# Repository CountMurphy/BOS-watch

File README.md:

Brotherhood of Steel Watch
========================

Ad Victoriam brother!

The BOS watch is the second version of my GPS enabled wristwatches. Stripped of the non used features and annoyances of the [Pipman](https://random-hackery.net/post/pipman-gps-watch/) , the BOS watch contains all things a man traveling the wastes could want

[Official Page](https://random-hackery.net/post/bos-watch/)

Features
---------------
- GPS time syncing - get local time anywhere on earth at power up

- Tilt compensated compass (with LED directional indicators and exact heading information)

- Stop watch / countdown timer

- Speaker (Plays the fallout theme!)

- TV B-gone

- A Frickn' Laser!&trade;

- Low power usage

- USB charging

-  Gieger Counter sound emulator (planned at least)

- Retro look and feel using custom DIP switches (with 7 operating modes) and 1970's era calculator display bubble LEDs

Tech
---------
The BOS watch uses an arm processor and C (Huzzah! No more awful propeller spin code)

License
----------
[DBAD](https://github.com/philsturgeon/dbad/blob/master/LICENSE-en.md)

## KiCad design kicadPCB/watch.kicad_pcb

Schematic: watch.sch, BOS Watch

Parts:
12CR2: 10K; SPARKFUN-RESISTORS_0603-RES
C1, C2: 1uf; SPARKFUN_0603
C3, C4: 4.7uF; SPARKFUN-CAPACITORS_0603-CAP
C5, C6, C7, C8: .1uf; SPARKFUN_0603
C9: .001uf; SPARKFUN_0603
COMPCAP46: .1uf; SPARKFUN_0603
D1, D2, D3, D4, D5: LED; LED_D5.0mm
DISP1, DISP2: 7-SEGMENT-4DIGIT-COUNTER-HP-BUBBLE; SPARKFUN-DISPLAYS_DIL12
GPTX46: 330; SPARKFUN-RESISTORS_0603-RES
I2CR1: 10K; SPARKFUN-RESISTORS_0603-RES
IC1: ISL1209; ADAFRUIT_MSOP10
J1: USB_OTG; USB_Micro-B
LASER46: LD; PHOTONICS_LD-FLUSH-WITH-JUMPER
LED1: EAGLE-LTSPICE_LED_SML0603
LIPO46: SPARKFUN-CONNECTORS_JST-2-SMD
LS1: Speaker; ADAFRUIT_PS12
M1: BOS_LIBS_SWD_BREAKOUTS; BOS_LIBS_SWD2
Q1: Q_PNP_CEB; SOT-23
R1: 2K; SPARKFUN-RESISTORS_0603-RES
R2: 470; SPARKFUN-RESISTORS_0603-RES
R3, R4, R5, R6, R7, R8, R9, R10: 330; SPARKFUN-RESISTORS_0603-RES
R11, R12, R13, R14, R15: 220Ohm; SPARKFUN-RESISTORS_0603-RES
R16: 10; SPARKFUN-RESISTORS_0603-RES
R17, R26, R27, R29, R30: 10K; SPARKFUN-RESISTORS_0603-RES
R18: 330k; R_0603_1608Metric
S11: EG1213; ADAFRUIT_EG1213
T1: BC850; TRANSISTOR_SOT23
U1: ADAFRUIT_FGPMMOPA6H
U2: MKL27Z256VLH4; FREESCALE_LQFP-64_10X10X1.6
U$1: HMC6343A; SPARKFUN_LCC36
U$2: MCP73831; GEEKAMMO_SOT23-5
U$3, U$7, U$8, U$9: DIPS; BOS_LIBS_DIPS
U$4, U$5: 74HC595PW; BOS_LIBS_74HC595PW
Y1: Crystal; CRYSTAL_TC26H

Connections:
/N$1: U$1.22 (CS), U$1.35 (CSC)
/N$2: U2.15 (VREFL), U2.16 (VSSA)
/N$3: C4.2, LIPO46.2 (+), S11.2, U$2.3 (VBAT)
/N$4: C3.2, J1.1 (VBUS), LED1.A, U$2.4 (VDD)
/N$5: LED1.C, R2.1
/N$6: C2.1, C9.1, Q1.3 (C), U1.P$1 (VCC)
/N$7: R2.2, U$2.1 (STAT)
/N$8: R1.1, U$2.5 (PROG)
/N$9: DISP1.1 (D1), R3.1
/N$10: DISP1.10 (D2), R5.1
/N$11: DISP1.12 (A), DISP2.12 (A), U$4.Q0
/N$12: DISP1.4 (D3), R6.1
/N$13: DISP1.6 (D4), R4.1
/N$14: DISP2.1 (D1), R7.1
/N$15: DISP2.10 (D2), R8.1
/N$16: DISP1.7 (G), DISP2.7 (G), U$4.Q6
/N$17: DISP1.5 (DP), DISP2.5 (DP), U$4.Q7
/N$18: R9.2, U$5.Q6
/N$19: DISP1.9 (F), DISP2.9 (F), U$4.Q5
/N$20: DISP2.4 (D3), R9.1
/N$21: DISP1.8 (D), DISP2.8 (D), U$4.Q3
/N$22: R8.2, U$5.Q5
/N$23: R7.2, U$5.Q4
/N$24: R4.2, U$5.Q3
/N$25: R6.2, U$5.Q2
/N$26: DISP2.6 (D4), R10.1
/N$27: R3.2, U$5.Q0
/N$28: U$4.Q7S, U$5.DS
/N$29: R10.2, U$5.Q7
/N$30: GPTX46.1, U1.P$9 (TX)
/N$31: R5.2, U$5.Q1
/N$35: D4.1 (K), R12.2
/N$36: D5.1 (K), R11.2
/N$37: D2.1 (K), R14.2
/N$38: D3.1 (K), R13.2
/N$39: D1.1 (K), R15.2
/N$40: LASER46.C, R16.1
/N$41: R16.2, T1.3 (C)
/N$43: IC1.1 (XTALI), Y1.2
/N$44: IC1.2 (XTALO), Y1.1
/N$47: DISP1.2 (E), DISP2.2 (E), U$4.Q4
/N$50: DISP1.11 (B), DISP2.11 (B), U$4.Q1
/N$51: DISP1.3 (C), DISP2.3 (C), U$4.Q2
/PTA0: M1.2 (SWD_CLK), U2.22 (PTA0)
/PTA1: R26.2, U2.23 (PTA1), U$7.VCC (V)
/PTA3: M1.1 (SWD_DIO), U2.25 (PTA3)
/PTA4: R27.2, U2.26 (PTA4), U$3.VCC (V)
/PTA5: U2.27 (PTA5)
/PTA12: U2.28 (PTA12)
/PTA13: U2.29 (PTA13)
/PTA18: U2.32 (PTA18)
/PTA19: U2.33 (PTA19)
/PTB1: U2.36 (PTB1)
/PTB2: U2.37 (PTB2)
/PTB3: U2.38 (PTB3)
/PTB16: U2.39 (PTB16), U$4.DS
/PTB17: U2.40 (PTB17)
/PTB18: U2.41 (PTB18), U$4.OE, U$5.OE
/PTB19: U2.42 (PTB19)
/PTC0: U2.43 (PTC0)
/PTC2: U2.45 (PTC2)
/PTC3: U2.46 (PTC3/LLWU_P7), U$4.SHCP, U$5.SHCP
/PTC4: R18.2, U2.49 (PTC4/LLWU_P8)
/PTC7: U2.52 (PTC7)
/PTC8: 12CR2.1, IC1.8 (SCL), U2.53 (PTC8), U$1.32 (SCL)
/PTC9: I2CR1.1, IC1.7 (SDA), U2.54 (PTC9), U$1.36 (SDA)
/PTC10: U1.P$5 (3D-FIX), U2.55 (PTC10)
/PTC11: U2.56 (PTC11)
/PTD1: D2.2 (A), U2.58 (PTD1)
/PTD2: GPTX46.2, U2.59 (PTD2)
/PTD3: D5.2 (A), U2.60 (PTD3)
/PTD4: U2.61 (PTD4/LLWU_P14), U$4.STCP, U$5.STCP
/PTD5: D4.2 (A), U2.62 (PTD5)
/PTE0: D3.2 (A), U2.1 (PTE0)
/PTE1: R17.1, T1.1 (B), U2.2 (PTE1)
/PTE20: D1.2 (A), U2.9 (PTE20)
/PTE24: R29.1, U2.20 (PTE24), U$9.VCC (V)
/PTE25: R30.2, U2.21 (PTE25), U$8.VCC (V)
/PTE30: LS1.1, U2.18 (PTE30)
GND: C1.2, C2.2, C3.1, C4.1, C5.1, C6.1, C7.1, C8.1, C9.2, COMPCAP46.2, IC1.4 (GND), J1.5 (GND), LIPO46.1 (-), LS1.2, M1.3 (GND), R1.2, R11.1, R12.1, R13.1, R14.1, R15.1, R17.2, T1.2 (E), U1.P$3 (GND), U1.P$8 (GND), U1.P$12 (GND), U1.P$19 (GND), U2.4 (VSS_2), U2.31 (VSS_3), U2.47 (VSS), U$1.25 (GND), U$1.29 (GND), U$2.2 (VSS), U$3.GND, U$4.GND, U$5.GND, U$7.GND, U$8.GND, U$9.GND
unnamed: Q1.1 (B), R18.1

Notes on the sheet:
place near MCU VCC

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
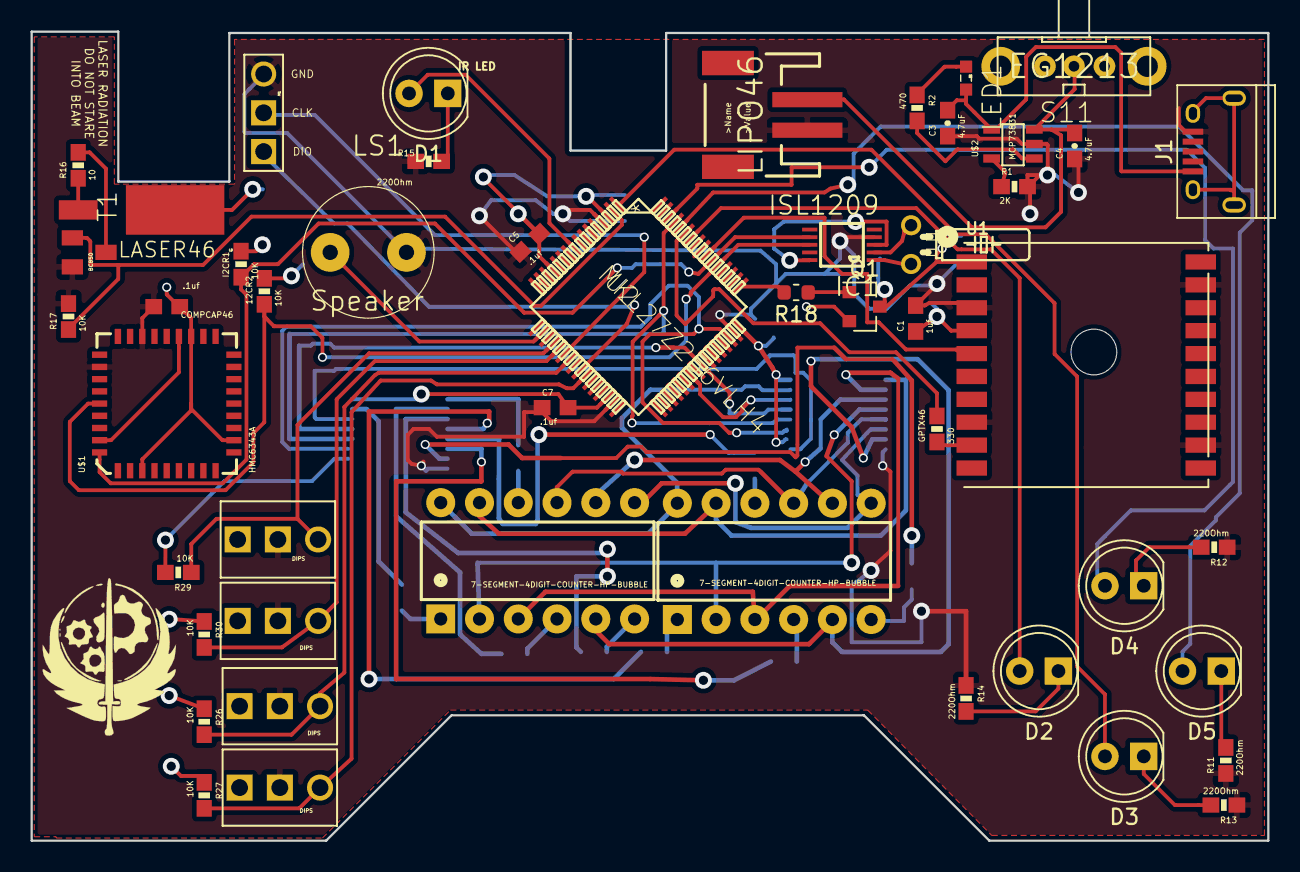
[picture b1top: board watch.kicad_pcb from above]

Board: 2 copper layers, 81.0 x 53.0 mm, 63 parts (0 on the bottom side), 68 nets.

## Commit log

2016-03-25 Added
2016-04-26 base layout
2016-04-26 made less messy, added libs
2016-04-26 wired more components
2016-04-30 added swd breakouts
2016-04-30 added charging unit
2016-05-01 added labels
2016-05-01 added pull up resistors
2016-05-20 started register lib
2016-05-20 added pads
2016-05-20 added shift regs to board
2016-05-21 finished first run of shift registers
2016-05-21 wired registers to board
2016-05-21 wired shift regs
2016-05-21 added compass leds
2016-05-21 added IR led.
2016-05-21 moved 5 way switch wiring
2016-05-22 added laser diode for lulz
2016-05-22 fixed gps fett
2016-05-22 cleaned up gps, added label for gps cap
2016-05-22 added vback cap
2016-05-22 fixed gps cap
2016-05-22 added mcu caps
2016-05-22 added readme
2016-05-22 added ssl for image
2016-05-22 added RTC crystal
2016-05-22 fixed typo in read me
2016-05-23 I think the SR clocks are now wired correctly?
2016-05-24 Moved Resistors from digit pins to segment pins and moved README image location to private server
2016-05-25 added control switch resistors
2016-07-08 reduced the amount of display resistors by more than half
2016-07-08 placement
2016-07-08 placed brd resistors
2016-07-09 added polygons
2016-07-09 top row hooked up
2016-07-09 wired most of the led display. TODO: wire SR together. God help me
2016-07-10 fixed vcc layer
2016-07-10 wired more of the SR
2016-07-19 wired all SR but one pin
2016-07-22 w00t! wired all SR
2016-07-22 cleaned up crap
2016-07-22 wired more resistors and traces
2016-08-27 wired charging circuit
2016-08-27 moved clock, rewired gps
2016-08-27 rewired gps
2016-08-27 laser wired
2016-08-27 refactored charging circuit and add caps to it
2016-08-28 wired compass LEDs. good god this thing is a mess
2016-08-28 removed airwires, added decoupling caps
2016-09-03 wired swd
2016-09-03 fixed some fuck ups
2016-09-03 moar refactoring
2016-09-05 fixed more wiring issues. started i2c
2016-09-05 fixed mroe air wires
2016-09-15 wired decoupling caps
2016-09-15 moved IR for smaller form factor
2016-09-18 all but one decoup cap done
2016-09-18 finished last decoupling cap
2016-09-27 added gps tx resistor
2016-09-27 altered values on gps caps
2016-09-27 finished adding gps caps per https://cdn-shop.adafruit.com/datasheets/GlobalTop-FGPMMOPA6H-Datasheet-V0A.pdf page 26
2016-10-18 added dip switches. need to check spaces for compass.
2016-10-18 fixed last air wire
2016-10-23 moved compass further from switches
2016-10-23 started drc
2016-10-23 more drc work
2016-10-26 more drc, discovered cockup with trace overlap
2016-10-26 overlaps fixed, reintroduced airwires
2016-11-02 fixed air wires
2016-11-18 final changes for drc
2016-11-19 added brand logo to rear (giggity)
2016-11-26 Board reshaped
2017-01-13 moved usb
2017-01-24 removed drill hole replaced with battery wire notch
2017-01-24 fixed bad dip package
2017-02-19 converted to kicad
    Eagle changed its licensing in a super dickish way. Done with that
2017-02-20 added laser warning text
2017-02-28 added clearer labels
2017-05-01 added BOM because KIcad BOM is terribad
2017-05-01 added KSDK and build scripts
2017-05-06 Added cmake files
2017-05-06 added missing gdb file for firmware upload
2017-05-06 test code
2017-05-08 test push for new git server
2017-05-08 removed garbage files
2017-05-09 compass test code, halts after send
2017-05-10 more testing
2017-05-10 added i2c thing
2017-05-10 fixed stupid sdk copy
2017-05-27 got i2c working
2017-06-06 minor improvments
2017-06-06 fixed spi1
2017-06-06 fixed resistor vals
2017-06-06 fixed uart gps
2017-06-07 moved OE to a timer pin to control display brightness
2017-06-07 removed large retarded vias to better enable trace navigation
2017-06-07 wired storage clock together for SR
2017-06-08 fixed laser label
2017-06-09 fixed compass orientation
2017-06-09 fixed clock crystal
2017-10-08 blinken lights
2017-10-08 seperated logic
2017-10-08 removed warnings
2017-12-21 added char dictionary
2017-12-21 refactored
2017-12-21 added add decimal method
2017-12-21 display is working
2017-12-21 removed warnings and unneeded code
2017-12-25 lower case g
2017-12-25 1st part of centering done
2017-12-27 at horse shit solution
2017-12-27 feels close
2017-12-27 feels close2
2017-12-27 evens work, not odds
2017-12-27 odds work
2018-01-01 multiplexing works, but is dim
2018-01-01 a tad brighter now
2018-01-16 made screen less nausiating
2018-01-17 added through hole usb
2018-01-17 fixed bad reset on SRs
2018-01-18 reversed IR LED
2018-01-18 fixed pnp
2018-01-21 fixed Laser npn, fixed laser and led south from bridge
2018-01-22 fixed labels
2018-02-13 plays fallout theme song
2018-02-13 turned screen back on
2018-02-13 added buzzer files I forgot to include (oops)
2018-03-10 added Y to dictionary
2018-03-28 updated ignore
2018-03-31 Added RTC functions
2018-04-26 Added GPS and refactored bad code
2018-05-02 clock menu done
2018-05-02 Added switch menu system
2018-05-02 RAD reader online
2018-05-02 fixed heisenbug
2018-05-02 can now interrupt song
2018-05-03 now prompts for dst
2018-05-06 Added scrolling text
2018-05-06 gps Menu done. Test release mode!!!
2018-05-08 Compass Modes added
2018-05-08 removed compiler warning
2018-05-09 stop watch works
2018-05-12 Added Count down timer
2018-05-14 refactored code. issue #5
2018-05-14 added laser code, but laser will not fire. Hardware issue
2018-05-20 added case
2018-05-20 mocked board
2018-05-23 Created Botton of case
2018-05-31 fixed debug gps bug
2018-07-25 compass directional LEDs fixed
2018-07-26 added pwr options, but going to HIGH from anything destroys the buzzer
2018-07-26 added pwr management definitions
2018-07-26 fixed compass again
2018-07-26 Completed Case Work
2018-08-04 fixed date parse bug
2018-08-04 gps case adjust for second build
2018-08-07 shorted led cover
2018-08-09 fixed compass power bleed
2018-09-25 Fixed date parsing, again
2018-10-13 typo in url
2018-10-26 fixed countdown display over 10
2018-10-30 forgot to convert to ascii
2018-11-16 refactored maths
2019-01-23 tweaked battery depth in case
2019-01-24 added low power mode request option on boot
2019-01-24 fixed power drain on standby.
2019-01-26 added removed display line
2019-01-26 fixed date flicker
2019-01-26 fixed compass heading precision
2019-01-26 added take on me
2019-01-27 fixed easily breakable screw
2019-02-02 removed low power flicker
2019-02-02 added pnp resistor
2019-02-04 added home page
2019-02-04 spelling
2019-03-02 Fixed GPS non display bug
2019-03-05 added case nub to prevent opening
2019-06-16 added tilt detection
2019-07-14 Revert "added tilt detection" was supposed to save battery...it doesn't
    This reverts commit f5f9ec7ae5f1f808401d766e55b7d08ef72a9010.
2019-08-16 Upated link
2023-08-30 added half mil spacer

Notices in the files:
parts and their libraries:
SparkFun-Displays: Licensing: Creative Commons ShareAlike 4.0 International - https://creativecommons.org/licenses/by-sa/4.0
